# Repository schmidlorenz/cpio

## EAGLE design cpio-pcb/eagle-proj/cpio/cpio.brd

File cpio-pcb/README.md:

# Overview PCB Design

The CPIO [PCB](https://en.wikipedia.org/wiki/Printed_circuit_board) is a small extension board for the Raspberry Pi which connects over the GPIO header (40 pins). It interfaces with multiple sensors such as:
 - temperature
 - humidity
 - brightness

and multiple actuators such as:
 - heating pads
 - ventilation fans
 - water pumps
 - lights

The schematic and layout of the PCB are design with Cadsoft's [Eagle](http://www.cadsoft.de/download-eagle/).

## Structure

The two folder with the prefix "eagle-" are used by Eagle:
 * [eagle-lbr](eagle-lbr/) contains the component library used in the design in addition to the [SparkFun](https://github.com/sparkfun/SparkFun-Eagle-Libraries) and [Adafruit](https://github.com/adafruit/Adafruit-Eagle-Library) library
 * [eagle-proj](eagle-proj/) contains the different prototype designs composed of layout and schematic files

The [components](components/) folder contains the part list of all used components as well as their documentation.

## Eagle Grid Settings

In order to have correct alignment of all components between different developers please use the following grid settings:

 - Grid: 0.635mm
 - Alt Grid: 0.127mm

The default setting can be changed in `[Eagle Install Dir]/scr/eagle.src`:
````
BRD:
Grid mm 0.635 on;
Grid alt mm 0.127;
````

## git diff

In order to be able to `git diff` for Eagle schematic (`.sch`) and layout files (`.brd`) use the [eagle-automation](https://github.com/guyzmo/eagle-automation) Python tool (also called `pea`) which generates images highlighting the differences visually.
It can be installed over [`pip`](https://pip.pypa.io/en/stable/):

    pip3 install eagle_automation

**Note:** Despite that a Python egg for Python 2.7 is available it seems as if the tool requires to be run with Python 3.

After installation to show differences to the design that have not yet been committed use the following command

    git difftool -t eaglediff

**Note:** The `pea` tool contains further functions allowing to generate for example a bill of material but most of it seem to be broken at the current moment (see [#5](https://github.com/guyzmo/eagle-automation/issues/5)). Instructions on how to use them will be added here once the issues are fixed.

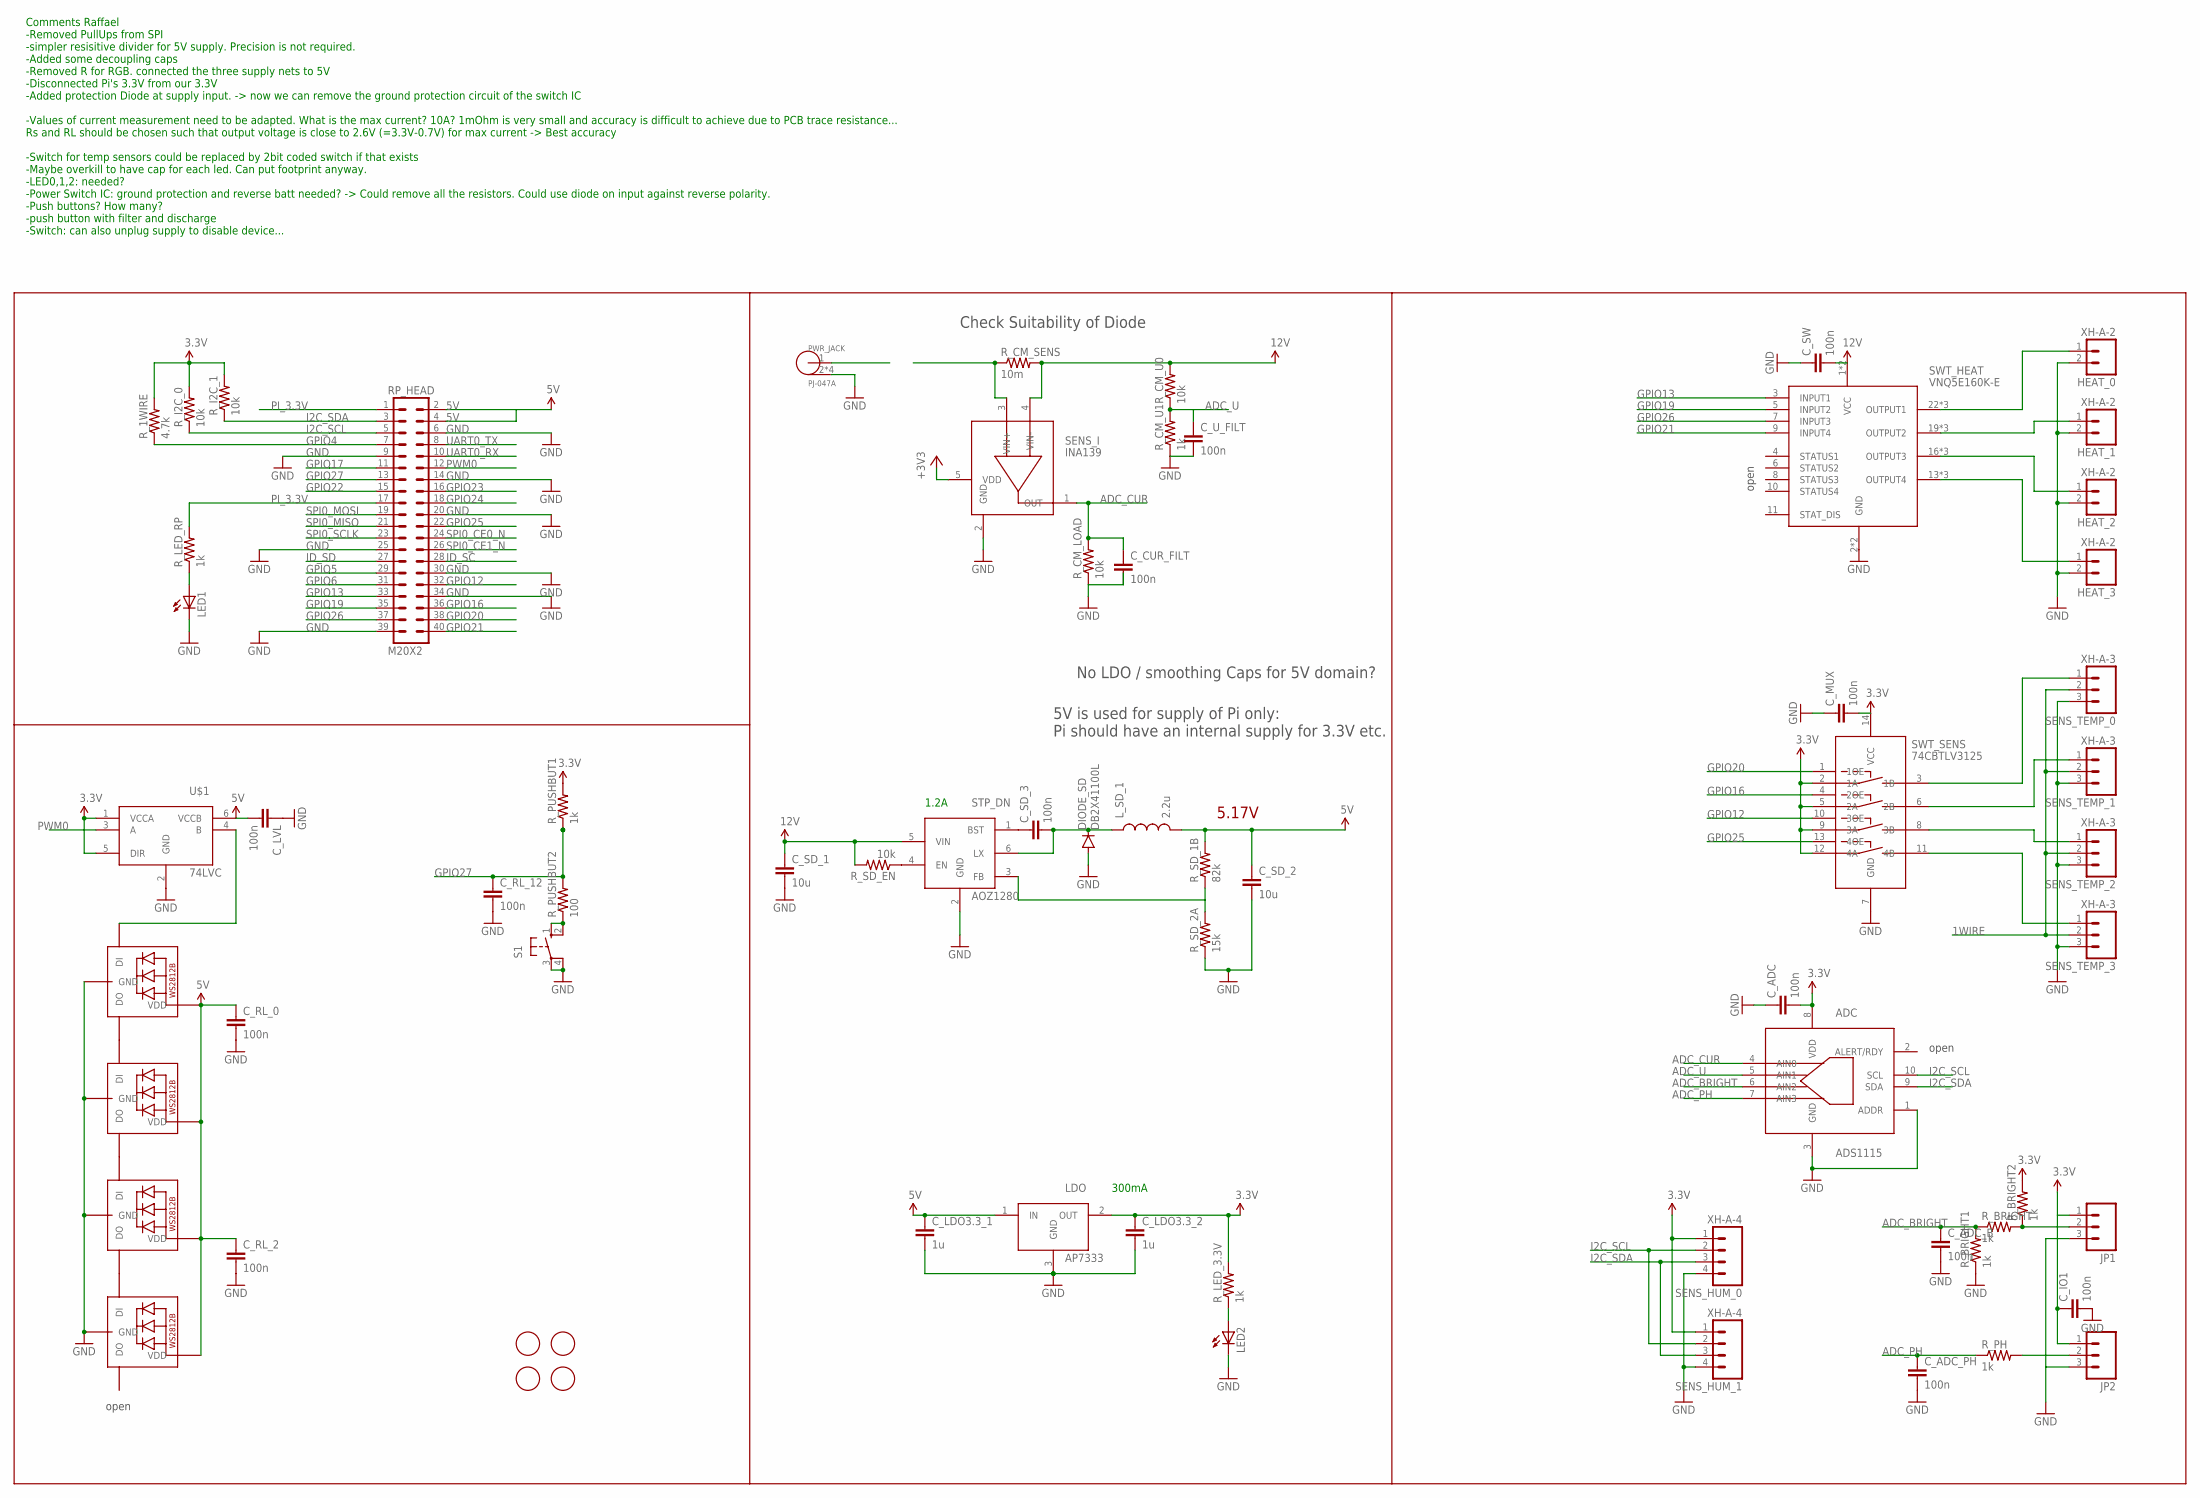
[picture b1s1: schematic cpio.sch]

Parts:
ADC: ADS1115; TFSOP-10
C_ADC: 100n; 0805
C_ADC_B: 100n; 0805
C_ADC_PH: 100n; 0805
C_CUR_FILT: 100n; 0805
C_IO1: 100n; 0805
C_LDO3.3_1, C_LDO3.3_2: 1u; 0805
C_LVL: 100n; 0805
C_MUX: 100n; 0805
C_RL_0, C_RL_2, C_RL_12: 100n; 0805
C_SD_1, C_SD_2: 10u; 0805
C_SD_3: 100n; 0805
C_SW: 100n; 0805
C_U_FILT: 100n; 0805
DIODE_SD: DB2X41100L; SOD-123FL
HEAT_0, HEAT_1, HEAT_2, HEAT_3: XH-A-2
JP1, JP2: M03PTH; 1X03
LDO: AP7333; SOT23-3
LED1, LED2: LEDSML0805; SML0805
L_SD_1: 2.2u; 0805
PWR_JACK: PJ-047A
RL_HEAT_0, RL_HEAT_1, RL_HEAT_2, RL_HEAT_3: WS2812B5050; WS2812B
RP_HEAD: M20X2; 2X20
R_1WIRE: 4.7k; 0805
R_BRIGHT, R_BRIGHT1, R_BRIGHT2: 1k; 0805
R_CM_LOAD: 10k; 0805
R_CM_SENS: 10m; 0805
R_CM_U0: 10k; 0805
R_CM_U1: 1k; 0805
R_I2C_0, R_I2C_1: 10k; 0805
R_LED_3.3V: 1k; 0805
R_LED_RP: 1k; 0805
R_PH: 1k; 0805
R_PUSHBUT1: 1k; 0805
R_PUSHBUT2: 100; 0805
R_SD_1B: 82k; 0805
R_SD_2A: 15k; 0805
R_SD_EN: 10k; 0805
S1: 10-XX; B3F-10XX
SENS_HUM_0, SENS_HUM_1: XH-A-4
SENS_I: INA139; SOT23-5
SENS_TEMP_0, SENS_TEMP_1, SENS_TEMP_2, SENS_TEMP_3: XH-A-3
STP_DN: AOZ1280; SOT23-6
SWT_HEAT: VNQ5E160K-E; POWERSSO-24
SWT_SENS: 74CBTLV3125; TSSOP-14
U$1: 74LVC; SOT-363
U$3, U$4, U$5, U$6: SPACERHOLE; HOLE

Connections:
1WIRE: SENS_TEMP_0.2, SENS_TEMP_1.2, SENS_TEMP_2.2, SENS_TEMP_3.2
3.3V: ADC.8 (VDD), C_ADC.2, C_IO1.1, C_LDO3.3_2.1, JP1.1, JP2.1, LDO.2 (OUT), R_1WIRE.2, R_BRIGHT2.2, R_I2C_0.2, R_I2C_1.2, R_LED_3.3V.2, R_PUSHBUT1.2, SENS_HUM_0.1, SENS_HUM_1.1, SWT_SENS.2 (1A), SWT_SENS.5 (2A), SWT_SENS.9 (3A), SWT_SENS.12 (4A), SWT_SENS.14 (VCC), U$1.1 (VCCA), U$1.5 (DIR)
3.3V1: C_MUX.2
3.3V2: C_SW.2
3.3V3: C_LVL.2
5V: C_LDO3.3_1.1, C_RL_0.1, C_RL_2.1, C_SD_2.1, LDO.1 (IN), L_SD_1.2, RL_HEAT_0.1-VDD (VDD), RL_HEAT_1.1-VDD (VDD), RL_HEAT_2.1-VDD (VDD), RL_HEAT_3.1-VDD (VDD), RP_HEAD.2, RP_HEAD.4, R_SD_1B.2, U$1.6 (VCCB)
12V: C_SD_1.1, R_CM_SENS.2, R_CM_U0.2, R_SD_EN.2, SENS_I.4 (VIN-), STP_DN.5 (VIN), SWT_HEAT.1 (VCC), SWT_HEAT.12 (VCC)
+3V3: SENS_I.5 (VDD)
ADC_BRIGHT: ADC.6 (AIN2), C_ADC_B.1, R_BRIGHT.1, R_BRIGHT1.2
ADC_CUR: ADC.4 (AIN0), C_CUR_FILT.1, R_CM_LOAD.2, SENS_I.1 (OUT)
ADC_PH: ADC.7 (AIN3), C_ADC_PH.1, R_PH.1
ADC_U: ADC.5 (AIN1), C_U_FILT.1, R_CM_U0.1, R_CM_U1.2
GND: ADC.1 (ADDR), ADC.3 (GND), C_ADC.1, C_ADC_B.2, C_ADC_PH.2, C_IO1.2, C_LDO3.3_1.2, C_LDO3.3_2.2, C_LVL.1, C_MUX.1, C_RL_0.2, C_RL_2.2, C_RL_12.2, C_SD_1.2, C_SD_2.2, C_SW.1, C_U_FILT.2, DIODE_SD.A, HEAT_0.2, HEAT_1.2, HEAT_2.2, HEAT_3.2, JP1.3, JP2.3, LDO.3 (GND), LED1.C, LED2.C, PWR_JACK.2 (GND), PWR_JACK.3 (GND), PWR_JACK.CASE0 (GND), PWR_JACK.CASE1 (GND), RL_HEAT_0.3-GND (GND), RL_HEAT_1.3-GND (GND), RL_HEAT_2.3-GND (GND), RL_HEAT_3.3-GND (GND), RP_HEAD.6, RP_HEAD.14, RP_HEAD.20, RP_HEAD.30, RP_HEAD.34, R_BRIGHT1.1, R_CM_LOAD.1, R_CM_U1.1, R_SD_2A.1, S1.3, S1.4 (P1), SENS_HUM_0.4, SENS_HUM_1.4, SENS_I.2 (GND), SENS_TEMP_0.3, SENS_TEMP_1.3, SENS_TEMP_2.3, SENS_TEMP_3.3, STP_DN.2 (GND), SWT_HEAT.2 (GND), SWT_HEAT.PAD (GND), SWT_SENS.7 (GND), U$1.2 (GND)
GPIO4: R_1WIRE.1
GPIO12: RP_HEAD.32, SWT_SENS.10 (3OE)
GPIO13: SWT_HEAT.3 (INPUT1)
GPIO16: RP_HEAD.36, SWT_SENS.4 (2OE)
GPIO19: SWT_HEAT.5 (INPUT2)
GPIO20: RP_HEAD.38, SWT_SENS.1 (1OE)
GPIO21: RP_HEAD.40, SWT_HEAT.9 (INPUT4)
GPIO23: RP_HEAD.16
GPIO24: RP_HEAD.18
GPIO25: RP_HEAD.22, SWT_SENS.13 (4OE)
GPIO26: SWT_HEAT.7 (INPUT3)
GPIO27: C_RL_12.1, R_PUSHBUT1.1, R_PUSHBUT2.2
I2C_SCL: ADC.10 (SCL), R_I2C_0.1, SENS_HUM_0.2, SENS_HUM_1.2
I2C_SDA: ADC.9 (SDA), R_I2C_1.1, SENS_HUM_0.3, SENS_HUM_1.3
ID_SC: RP_HEAD.28
unnamed: RP_HEAD.3, RP_HEAD.5, RP_HEAD.7, RP_HEAD.9, RP_HEAD.11, RP_HEAD.13, RP_HEAD.15, RP_HEAD.19, RP_HEAD.21, RP_HEAD.23, RP_HEAD.25, RP_HEAD.27, RP_HEAD.29, RP_HEAD.31, RP_HEAD.33, RP_HEAD.35, RP_HEAD.37, RP_HEAD.39
unnamed: R_PUSHBUT2.1, S1.1 (S), S1.2 (S1)
unnamed: R_SD_EN.1, STP_DN.4 (EN)
unnamed: JP2.2, R_PH.2
unnamed: C_SD_3.1, STP_DN.1 (BST)
unnamed: C_SD_3.2, DIODE_SD.C, L_SD_1.1, STP_DN.6 (LX)
unnamed: LED2.A, R_LED_3.3V.1
unnamed: SENS_TEMP_1.1, SWT_SENS.6 (2B)
unnamed: SENS_TEMP_0.1, SWT_SENS.3 (1B)
unnamed: SENS_TEMP_2.1, SWT_SENS.8 (3B)
unnamed: SENS_TEMP_3.1, SWT_SENS.11 (4B)
unnamed: LED1.A, R_LED_RP.1
unnamed: R_CM_SENS.1, SENS_I.3 (VIN+)
unnamed: HEAT_2.1, SWT_HEAT.16 (OUTPUT3), SWT_HEAT.17 (OUTPUT3), SWT_HEAT.18 (OUTPUT3)
unnamed: HEAT_1.1, SWT_HEAT.19 (OUTPUT2), SWT_HEAT.20 (OUTPUT2), SWT_HEAT.21 (OUTPUT2)
unnamed: HEAT_0.1, SWT_HEAT.22 (OUTPUT1), SWT_HEAT.23 (OUTPUT1), SWT_HEAT.24 (OUTPUT1)
unnamed: HEAT_3.1, SWT_HEAT.13 (OUTPUT4), SWT_HEAT.14 (OUTPUT4), SWT_HEAT.15 (OUTPUT4)
unnamed: JP1.2, R_BRIGHT.2, R_BRIGHT2.1
unnamed: RL_HEAT_2.2-DOUT (DO), RL_HEAT_3.4-DIN (DI)
unnamed: RL_HEAT_1.2-DOUT (DO), RL_HEAT_2.4-DIN (DI)
unnamed: RL_HEAT_0.2-DOUT (DO), RL_HEAT_1.4-DIN (DI)
unnamed: RL_HEAT_0.4-DIN (DI), U$1.4 (B)
PI_3.3V: RP_HEAD.1, RP_HEAD.17, R_LED_RP.2
PWM0: RP_HEAD.12, U$1.3 (A)
SPI0_CE0_N: RP_HEAD.24
SPI0_CE1_N: RP_HEAD.26
UART0_RX: RP_HEAD.10
UART0_TX: RP_HEAD.8

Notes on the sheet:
open
Comments Raffael -Removed PullUps from SPI -simpler resisitive divider for 5V supply. Precision is not required. -Added some decoupling caps -Removed R for RGB. connected the three supply nets to 5V -Disconnected Pi's 3.3V from our 3.3V -Added protection Diode at supply input. -> now we can remove 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
5.17V
5V is used for supply of Pi only: Pi should have an internal supply for 3.3V etc.
No LDO / smoothing Caps for 5V domain?
300mA
1.2A
Check Suitability of Diode

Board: 2 copper layers, 69 parts (2 on the bottom side), 41 nets, no tracks yet.

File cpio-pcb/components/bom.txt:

Partlist

Exported from cpio.sch at 21.12.15 22:32

EAGLE Version 7.5.0 Copyright (c) 1988-2015 CadSoft

Assembly variant: 

Part        Value          Device           Package     Library             Sheet

ADC         ADS1115        ADS1115          TFSOP-10    cpio                1
C_ADC       100n           CAP0805          0805        SparkFun-Passives   1
C_ADC_B     100n           CAP0805          0805        SparkFun-Passives   1
C_ADC_PH    100n           CAP0805          0805        SparkFun-Passives   1
C_CUR_FILT  100n           CAP0805          0805        SparkFun-Passives   1
C_IO1       100n           CAP0805          0805        SparkFun-Passives   1
C_LVL       100n           CAP0805          0805        SparkFun-Passives   1
C_MUX       100n           CAP0805          0805        SparkFun-Passives   1
C_RL_0      100n           CAP0805          0805        SparkFun-Passives   1
C_RL_2      100n           CAP0805          0805        SparkFun-Passives   1
C_RL_12     100n           CAP0805          0805        SparkFun-Passives   1
C_SD_3      100n           CAP0805          0805        SparkFun-Passives   1
C_SW        100n           CAP0805          0805        SparkFun-Passives   1
C_U_FILT    100n           CAP0805          0805        SparkFun-Passives   1
C_LDO3.3_1  1u             CAP0805          0805        SparkFun-Passives   1
C_LDO3.3_2  1u             CAP0805          0805        SparkFun-Passives   1
C_SD_1      10u            CAP0805          0805        SparkFun-Passives   1
C_SD_2      10u            CAP0805          0805        SparkFun-Passives   1
L_SD_1      2.2u           INDUCTOR0805     0805        SparkFun-Passives   1
R_CM_SENS   10m            RESISTOR0805-RES 0805        SparkFun-Passives   1
R_PUSHBUT2  100            RESISTOR0805-RES 0805        SparkFun-Passives   1
R_BRIGHT    1k             RESISTOR0805-RES 0805        SparkFun-Passives   1
R_CM_U1     1k             RESISTOR0805-RES 0805        SparkFun-Passives   1
R_LED_3.3V  1k             RESISTOR0805-RES 0805        SparkFun-Passives   1
R_LED_RP    1k             RESISTOR0805-RES 0805        SparkFun-Passives   1
R_PH        1k             RESISTOR0805-RES 0805        SparkFun-Passives   1
R_PUSHBUT1  1k             RESISTOR0805-RES 0805        SparkFun-Passives   1
R_1WIRE     4.7k           RESISTOR0805-RES 0805        SparkFun-Passives   1
R_CM_LOAD   10k            RESISTOR0805-RES 0805        SparkFun-Passives   1
R_CM_U0     10k            RESISTOR0805-RES 0805        SparkFun-Passives   1
R_I2C_0     10k            RESISTOR0805-RES 0805        SparkFun-Passives   1
R_I2C_1     10k            RESISTOR0805-RES 0805        SparkFun-Passives   1
R_SD_EN     10k            RESISTOR0805-RES 0805        SparkFun-Passives   1
R_SD_2A     15k            RESISTOR0805-RES 0805        SparkFun-Passives   1
R_SD_1B     82k            RESISTOR0805-RES 0805        SparkFun-Passives   1
LED1                       LEDSML0805       SML0805     led                 1
LED2                       LEDSML0805       SML0805     led                 1
RL_HEAT_0   WS2812B5050    WS2812B5050      WS2812B     adafruit            1
RL_HEAT_1   WS2812B5050    WS2812B5050      WS2812B     adafruit            1
RL_HEAT_2   WS2812B5050    WS2812B5050      WS2812B     adafruit            1
RL_HEAT_3   WS2812B5050    WS2812B5050      WS2812B     adafruit            1
DIODE_SD    DB2X41100L     DB2X41100L       SOD-123FL   cpio                1
HEAT_0      XH-A-2         XH-A-2           XH-A-2      cpio                1
HEAT_1      XH-A-2         XH-A-2           XH-A-2      cpio                1
HEAT_2      XH-A-2         XH-A-2           XH-A-2      cpio                1
HEAT_3      XH-A-2         XH-A-2           XH-A-2      cpio                1
SENS_TEMP_0 XH-A-3         XH-A-3           XH-A-3      cpio                1
SENS_TEMP_1 XH-A-3         XH-A-3           XH-A-3      cpio                1
SENS_TEMP_2 XH-A-3         XH-A-3           XH-A-3      cpio                1
SENS_TEMP_3 XH-A-3         XH-A-3           XH-A-3      cpio                1
SENS_HUM_0  XH-A-4         XH-A-4           XH-A-4      cpio                1
SENS_HUM_1  XH-A-4         XH-A-4           XH-A-4      cpio                1
JP1                        M03PTH           1X03        SparkFun-Connectors 1
JP2                        M03PTH           1X03        SparkFun-Connectors 1
RP_HEAD     M20X2          M20X2            2X20        SparkFun-Connectors 1
PWR_JACK    PJ-047A        PJ-047A          PJ-047A     cpio                1
S1                         10-XX            B3F-10XX    switch-omron        1
LDO         AP7333         AP7333           SOT23-3     cpio                1
SENS_I      INA139         INA139           SOT23-5     cpio                1
STP_DN      AOZ1280        AOZ1280          SOT23-6     cpio                1
SWT_HEAT    VNQ5E160K-E    VNQ5E160K-E      POWERSSO-24 cpio                1
SWT_SENS    74CBTLV3125    74CBTLV3125      TSSOP-14    cpio                1
U$1         74LVC          74LVC            SOT-363     cpio                1

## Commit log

2015-12-10 Inital commit
2015-12-10 Eagle lib structure
2015-12-10 created web app frontend toolchain
2015-12-10 added first web layout draft
2015-12-10 Added basic Readme files to web frontend
2015-12-11 added component list in xlsx-format, used following approach to make xlsx-file git diff compatible http://stackoverflow.com/questions/17083502/how-to-perform-better-document-version-control-on-excel-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
2015-12-11 updated component list (changes made by Raffael)
2015-12-11 added forgotten dependencies in bower.json
2015-12-11 improved web frontent toolchain with installer script
2015-12-11 added readme files for PCB section, explanation how to 'git diff' xlsx-files
2015-12-11 Include installation in readme of web frontend
2015-12-12 schematic update
2015-12-12 small changes to demonstrate git to Tatiana
2015-12-12 updated gitignore for eagle
2015-12-13 clean start with components population of Eagle library
2015-12-14 better web frontend folder and generation structure
2015-12-14 added browser-sync for web frontend
2015-12-14 Updated web frontend readme
2015-12-14 small change on web frontend readme
2015-12-14 Final changes on web front-end readme
2015-12-14 updated footprints and cleaned component list
2015-12-15 cleaned component list
2015-12-15 added symbols for all components
2015-12-15 added footprints for all components
2015-12-15 added all components in Eagle
2015-12-15 Level Shifter for RGB LED command
2015-12-15 schematic for power domains done
2015-12-16 added Level Shifter to Components
2015-12-16 updated component list with JST connectors
2015-12-16 smaller changes
2015-12-16 new XH connector components added
2015-12-17 larger PCB schematic updated, onlyUI missing
2015-12-17 smaller Typo corrections
2015-12-17 schematic ready for UX
2015-12-17 RGB LEDs added to schematic
2015-12-17 RGB LEDs added to schematic done
2015-12-17 Schematic completed with GPIOS
2015-12-18 First Review and modification of schematic
2015-12-19 PCB with RPI-Zero Outline
2015-12-19 scetch of PCB layout in order to see which components have to be removed
2015-12-19 schematic review: button and some R less
2015-12-19 board with zero outline
2015-12-19 rename brightness input. Now with gnd, signal, vcc
2015-12-19 clean up and deleting components
2015-12-19 Second Scetch of PCB layout with removed components
2015-12-20 rearranged PCB files and added readme on how to use git diff with Eagle files
2015-12-20 added configuration and requierements for the Python web app, added and updated README files
2015-12-20 Django web app initialized to basic structure
2015-12-20 Django: Initialized interface module
2015-12-21 Holes added to Components
2015-12-21 schematic revised and first BOM
2015-12-21 updated component list, ordered bom
2015-12-21 updated component list to bom
2015-12-21 added missing reference
2015-12-21 updated JST plugs
2015-12-21 updated Readme for Eagle Grid Settings
2015-12-21 schematic revs...
2015-12-23 cross-checked component list to order
2015-12-28 Clarify to use pip3

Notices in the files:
parts and their libraries:
SparkFun-Passives: Licensing: Creative Commons ShareAlike 4.0 International - https://creativecommons.org/licenses/by-sa/4.0
